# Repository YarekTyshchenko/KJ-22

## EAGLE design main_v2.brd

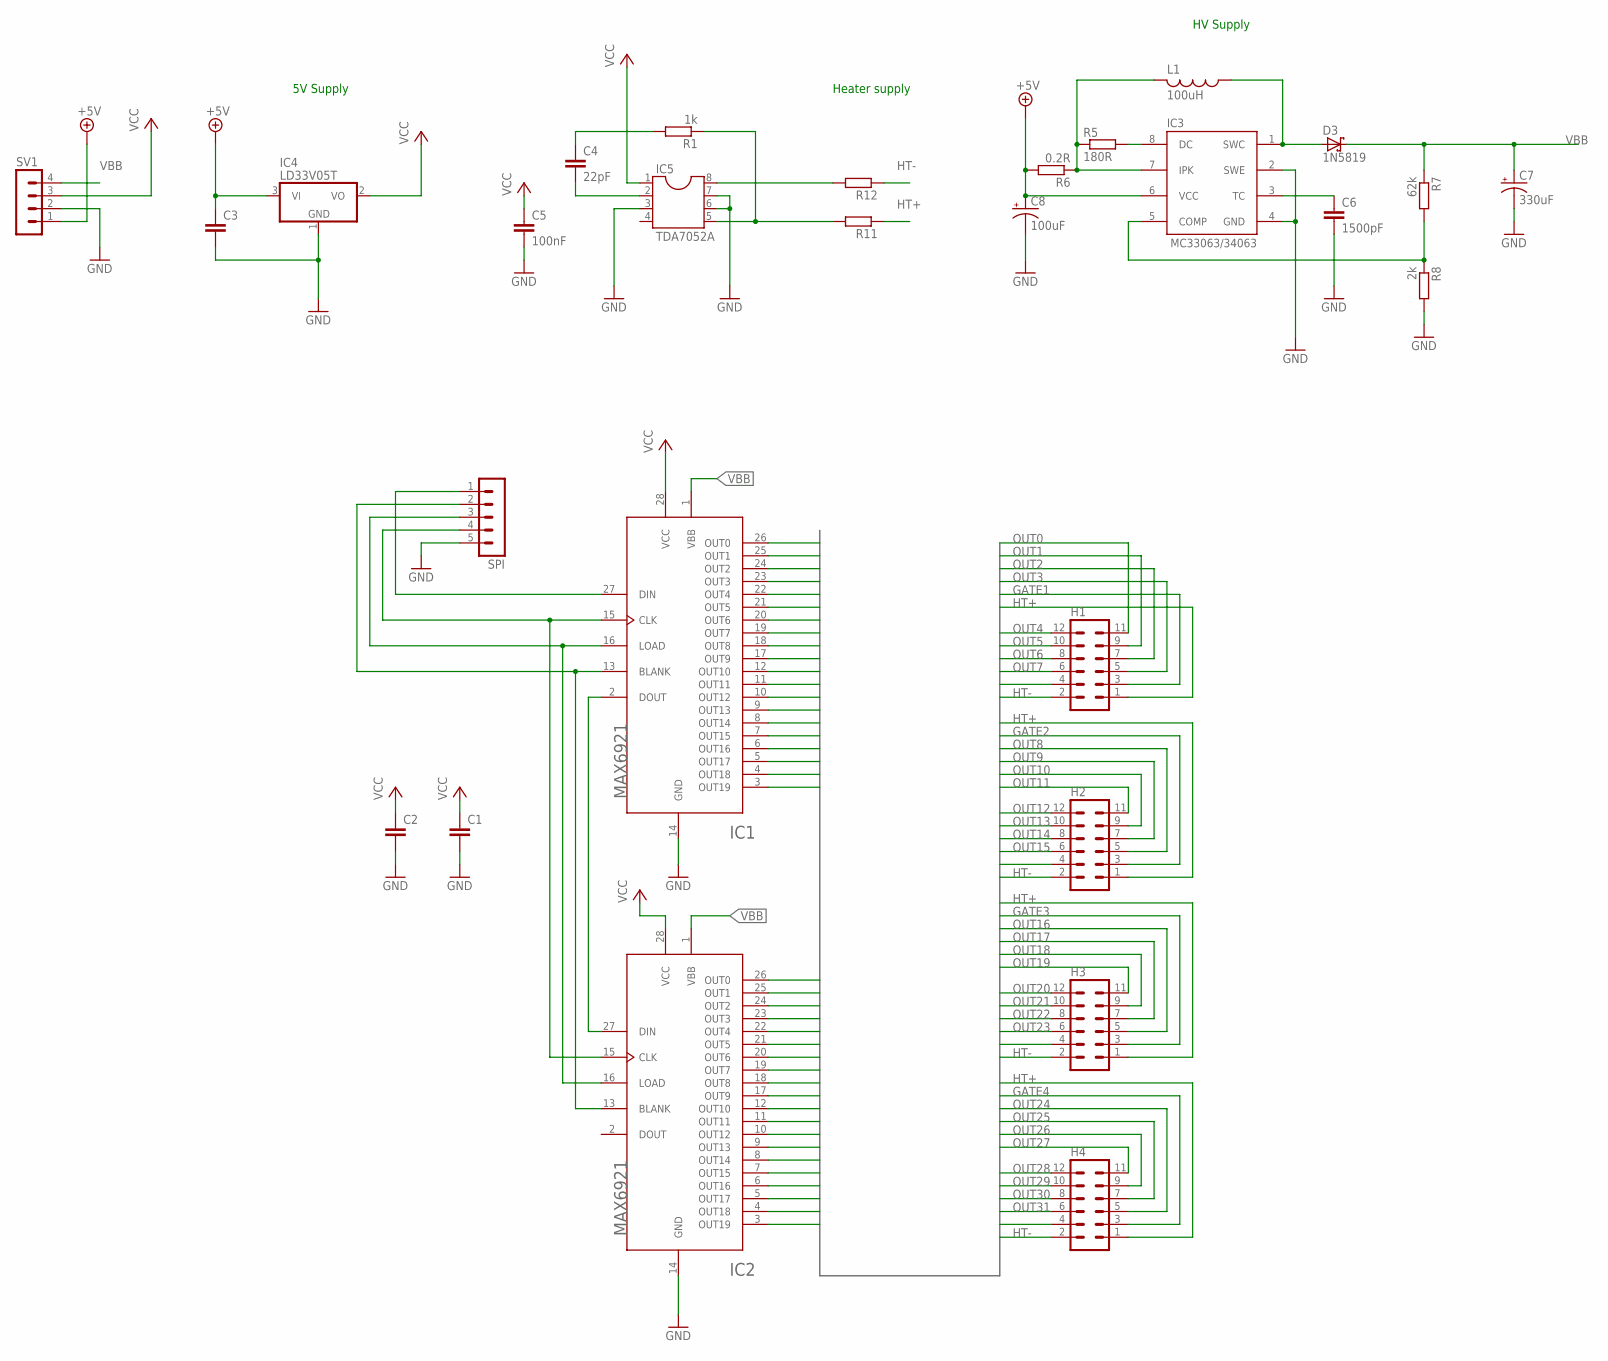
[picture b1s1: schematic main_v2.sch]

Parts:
C1, C2, C3: C-EU025-025X050; C025-025X050
C4: 22pF; C025-025X050
C5: 100nF; C025-025X050
C6: 1500pF; C025-025X050
C7: 330uF; E3,5-8
C8: 100uF; E2,5-5
D3: 1N5819; DO35-7
H1, H2, H3, H4: MA06-2
IC1, IC2: MAX6921; PLCC-S28
IC3: MC33063; DIL08
IC4: LD33V05T; TO220H
IC5: TDA7052A; DIL08
L1: 100uH; 6000-XXXX-RC
R1: 1k; 0204/7
R5: 180R; 0204/7
R6: 0.2R; 0207/10
R7: 62k; 0204/7
R8: 2k; 0204/7
R11, R12: R-EU_0204/7; 0204/7
SPI: MA05-1
SV1: MA04-1

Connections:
+5V: C3.1, C8.+, IC3.6 (VCC), IC4.3 (VI), R6.2, SV1.1
GATE1: H1.3, IC2.12 (OUT10)
GATE2: H2.3, IC2.18 (OUT8)
GATE3: H3.3, IC1.12 (OUT10)
GATE4: H4.3, IC1.25 (OUT1)
GND: C1.2, C2.2, C3.2, C5.2, C6.2, C7.-, C8.-, IC1.14 (GND), IC2.14 (GND), IC3.2 (SWE), IC3.4 (GND), IC4.1 (GND), IC5.3, IC5.6, IC5.7, R8.2, SPI.5, SV1.2
HT+: H1.1, H2.1, H3.1, H4.1, R11.1
HT-: H1.2, H2.2, H3.2, H4.2, R12.1
MOSI: IC1.27 (DIN), SPI.1
unnamed: IC1.2 (DOUT), IC2.27 (DIN)
unnamed: IC5.8, R12.2
unnamed: IC1.13 (BLANK), IC2.13 (BLANK), SPI.2
unnamed: IC1.16 (LOAD), IC2.16 (LOAD), SPI.3
unnamed: C6.1, IC3.3 (TC)
unnamed: IC5.5, R1.1, R11.2
unnamed: D3.A, IC3.1 (SWC), L1.1
unnamed: IC3.7 (IPK), L1.2, R5.1, R6.1
unnamed: IC3.8 (DC), R5.2
unnamed: C4.2, IC5.2
unnamed: IC3.5 (COMP), R7.2, R8.1
unnamed: C4.1, R1.2
OUT0: H1.11, IC2.10 (OUT12)
OUT1: H1.9, IC2.7 (OUT15)
OUT2: H1.7, IC2.5 (OUT17)
OUT3: H1.5, IC2.11 (OUT11)
OUT4: H1.12, IC2.9 (OUT13)
OUT5: H1.10, IC2.8 (OUT14)
OUT6: H1.8, IC2.6 (OUT16)
OUT7: H1.6, IC2.3 (OUT19)
OUT8: H2.5, IC2.21 (OUT5)
OUT9: H2.7, IC2.23 (OUT3)
OUT10: H2.9, IC2.25 (OUT1)
OUT11: H2.11, IC2.19 (OUT7)
OUT12: H2.12, IC2.20 (OUT6)
OUT13: H2.10, IC2.26 (OUT0)
OUT14: H2.8, IC2.24 (OUT2)
OUT15: H2.6, IC2.22 (OUT4)
OUT16: H3.5, IC1.11 (OUT11)
OUT17: H3.7, IC1.8 (OUT14)
OUT18: H3.9, IC1.9 (OUT13)
OUT19: H3.11, IC1.10 (OUT12)
OUT20: H3.12, IC1.7 (OUT15)
OUT21: H3.10, IC1.6 (OUT16)
OUT22: H3.8, IC1.5 (OUT17)
OUT23: H3.6, IC1.3 (OUT19)
OUT24: H4.5, IC1.23 (OUT3)
OUT25: H4.7, IC1.21 (OUT5)
OUT26: H4.9, IC1.22 (OUT4)
OUT27: H4.11, IC1.19 (OUT7)
OUT28: H4.12, IC1.20 (OUT6)
OUT29: H4.10, IC1.18 (OUT8)
OUT30: H4.8, IC1.17 (OUT9)
OUT31: H4.6, IC1.24 (OUT2)
SCK: IC1.15 (CLK), IC2.15 (CLK), SPI.4
SPARE1: H1.4, IC2.4 (OUT18)
SPARE2: H2.4, IC2.17 (OUT9)
SPARE3: H3.4, IC1.4 (OUT18)
SPARE4: H4.4, IC1.26 (OUT0)
VBB: C7.+, D3.C, IC1.1 (VBB), IC2.1 (VBB), R7.1, SV1.4
VCC: C1.1, C2.1, C5.1, IC1.28 (VCC), IC2.28 (VCC), IC4.2 (VO), IC5.1, SV1.3

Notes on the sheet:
Heater supply
HV Supply
5V Supply

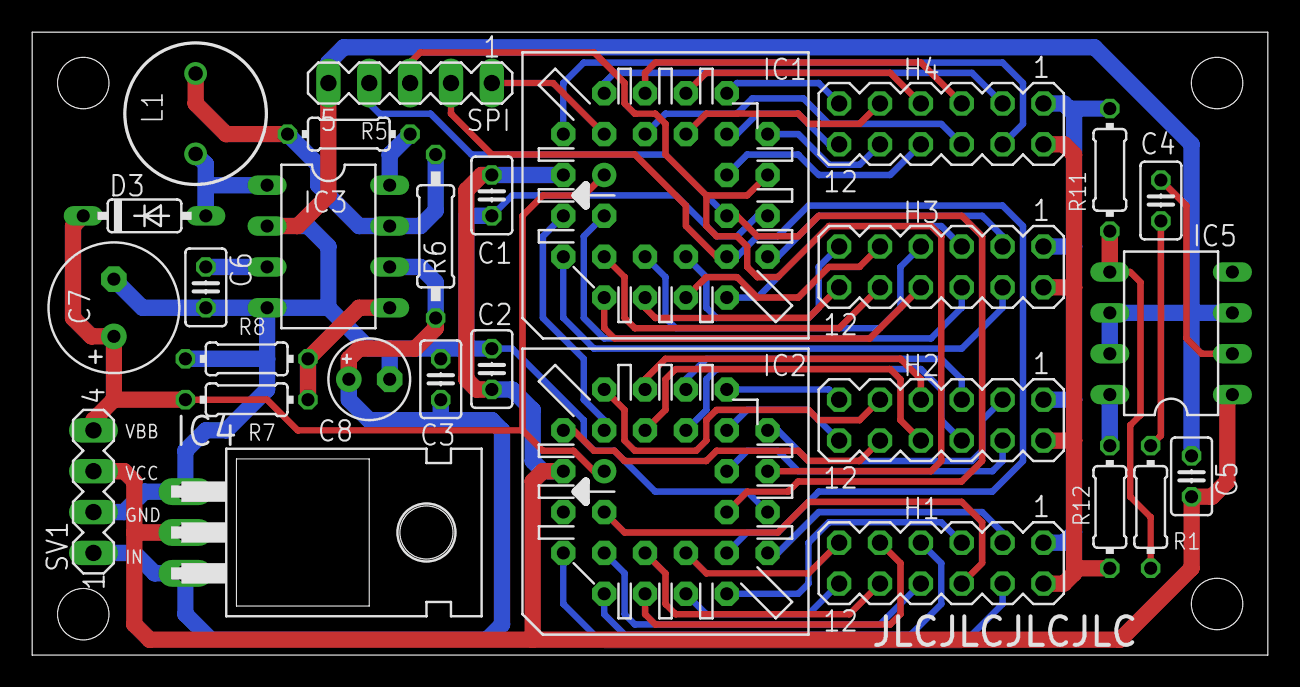
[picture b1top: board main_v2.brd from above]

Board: 2 copper layers, 76.8 x 38.7 mm, 28 parts (0 on the bottom side), 60 nets.

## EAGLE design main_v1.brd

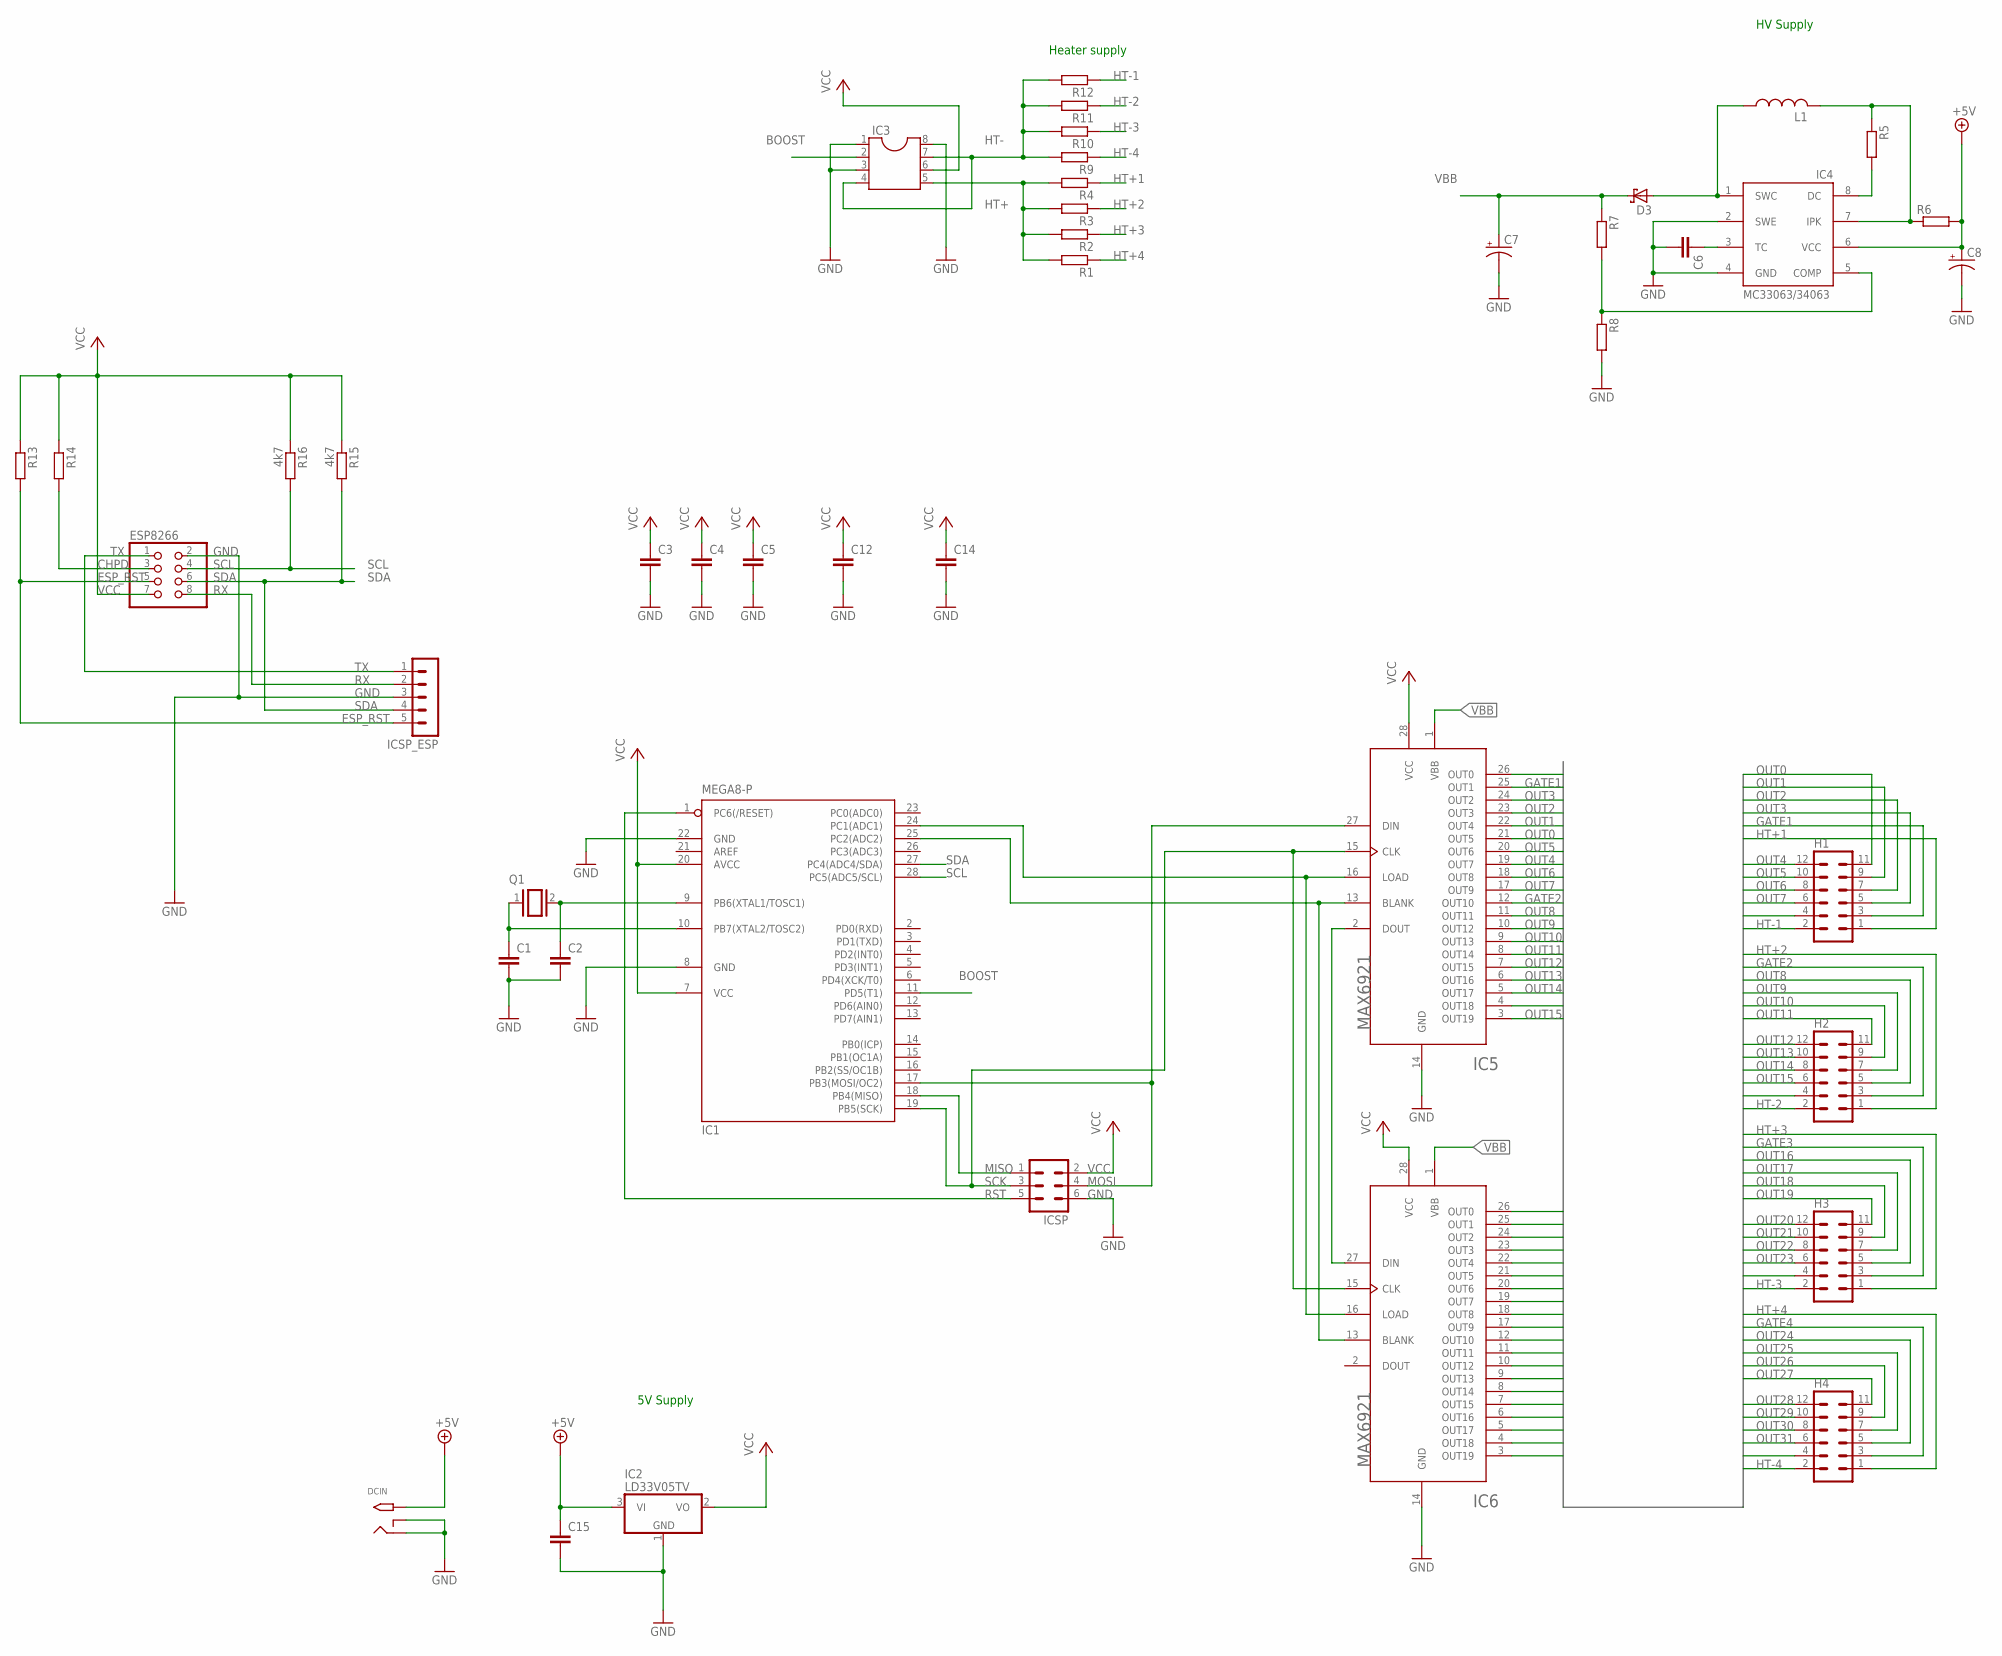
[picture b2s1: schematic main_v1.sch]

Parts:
C1, C2: C2.5/2; C2.5-2
C3, C4, C5, C6, C12, C14, C15: C-EU025-025X050; C025-025X050
C7: CPOL-USE3.5-8; E3,5-8
C8: CPOL-USE2.5-5; E2,5-5
D3: SCHOTTKY-DIODEDO35-7; DO35-7
DCIN: 2.1MMJACKTHM; PJ-102A
ESP8266: PINHD-2X4; 2X04
H1, H2, H3, H4: MA06-2
IC1: MEGA8-P; DIL28-3
IC2: LD33V05TV; TO220V
IC3: DIL8; DIL08
IC4: MC33063/MC34063P; DIL08
IC5, IC6: MAX6921; PLCC-S28
ICSP: MA03-2
ICSP_ESP: MA05-1
L1: L-US6000-XXX-RC; 6000-XXXX-RC
Q1: XTAL/S; QS
R1, R2, R3, R4, R5, R6, R7, R8, R9, R10, R11, R12, R14: R-EU_0204/7; 0204/7
R13: R-EU_0207/10; 0207/10
R15, R16: 4k7; 0204/7

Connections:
+5V: C8.+, C15.1, DCIN.TIP, IC2.3 (VI), IC4.6 (VCC), R6.2
BOOST: IC1.11 (PD5(T1)), IC3.2
CHPD: ESP8266.3, R14.2
ESP_RST: ESP8266.5, ICSP_ESP.5, R13.2
GATE1: H1.3, IC5.25 (OUT1)
GATE2: H2.3, IC5.12 (OUT10)
GATE3: H3.3, IC6.25 (OUT1)
GATE4: H4.3, IC6.12 (OUT10)
GND: C1.2, C2.2, C3.2, C4.2, C5.2, C6.2, C7.-, C8.-, C12.2, C14.2, C15.2, DCIN.RING, DCIN.RING_SW, ESP8266.2, IC1.8 (GND), IC1.22 (GND), IC2.1 (GND), IC3.1, IC3.3, IC3.8, IC4.2 (SWE), IC4.4 (GND), IC5.14 (GND), IC6.14 (GND), ICSP.6, ICSP_ESP.3, R8.2
HT+: IC3.5, R1.2, R2.2, R3.2, R4.2
HT+1: H1.1, R4.1
HT+2: H2.1, R3.1
HT+3: H3.1, R2.1
HT+4: H4.1, R1.1
HT-: IC3.4, IC3.7, R9.2, R10.2, R11.2, R12.2
HT-1: H1.2, R12.1
HT-2: H2.2, R11.1
HT-3: H3.2, R10.1
HT-4: H4.2, R9.1
MISO: IC1.18 (PB4(MISO)), ICSP.1
MOSI: IC1.17 (PB3(MOSI/OC2)), IC5.27 (DIN), ICSP.4
unnamed: IC5.2 (DOUT), IC6.27 (DIN)
unnamed: C1.1, IC1.10 (PB7(XTAL2/TOSC2)), Q1.1
unnamed: IC1.25 (PC2(ADC2)), IC5.13 (BLANK), IC6.13 (BLANK)
unnamed: IC1.24 (PC1(ADC1)), IC5.16 (LOAD), IC6.16 (LOAD)
unnamed: C6.1, IC4.3 (TC)
unnamed: C2.1, IC1.9 (PB6(XTAL1/TOSC1)), Q1.2
unnamed: D3.A, IC4.1 (SWC), L1.1
unnamed: IC4.7 (IPK), L1.2, R5.1, R6.1
unnamed: IC4.8 (DC), R5.2
unnamed: IC4.5 (COMP), R7.2, R8.1
OUT0: H1.11, IC5.21 (OUT5)
OUT1: H1.9, IC5.22 (OUT4)
OUT2: H1.7, IC5.23 (OUT3)
OUT3: H1.5, IC5.24 (OUT2)
OUT4: H1.12, IC5.19 (OUT7)
OUT5: H1.10, IC5.20 (OUT6)
OUT6: H1.8, IC5.18 (OUT8)
OUT7: H1.6, IC5.17 (OUT9)
OUT8: H2.5, IC5.11 (OUT11)
OUT9: H2.7, IC5.10 (OUT12)
OUT10: H2.9, IC5.9 (OUT13)
OUT11: H2.11, IC5.8 (OUT14)
OUT12: H2.12, IC5.7 (OUT15)
OUT13: H2.10, IC5.6 (OUT16)
OUT14: H2.8, IC5.5 (OUT17)
OUT15: H2.6, IC5.3 (OUT19)
OUT16: H3.5, IC6.24 (OUT2)
OUT17: H3.7, IC6.23 (OUT3)
OUT18: H3.9, IC6.22 (OUT4)
OUT19: H3.11, IC6.21 (OUT5)
OUT20: H3.12, IC6.19 (OUT7)
OUT21: H3.10, IC6.20 (OUT6)
OUT22: H3.8, IC6.18 (OUT8)
OUT23: H3.6, IC6.17 (OUT9)
OUT24: H4.5, IC6.11 (OUT11)
OUT25: H4.7, IC6.10 (OUT12)
OUT26: H4.9, IC6.9 (OUT13)
OUT27: H4.11, IC6.8 (OUT14)
OUT28: H4.12, IC6.7 (OUT15)
OUT29: H4.10, IC6.6 (OUT16)
OUT30: H4.8, IC6.5 (OUT17)
OUT31: H4.6, IC6.3 (OUT19)
RST: IC1.1 (PC6(/RESET)), ICSP.5
RX: ESP8266.8, ICSP_ESP.2
SCK: IC1.19 (PB5(SCK)), IC5.15 (CLK), IC6.15 (CLK), ICSP.3
SCL: ESP8266.4, IC1.28 (PC5(ADC5/SCL)), R16.2
SDA: ESP8266.6, IC1.27 (PC4(ADC4/SDA)), ICSP_ESP.4, R15.2
SPARE1: H1.4, IC5.26 (OUT0)
SPARE2: H2.4, IC5.4 (OUT18)
SPARE3: H3.4, IC6.26 (OUT0)
SPARE4: H4.4, IC6.4 (OUT18)
TX: ESP8266.1, ICSP_ESP.1
VBB: C7.+, D3.C, IC5.1 (VBB), IC6.1 (VBB), R7.1
VCC: C3.1, C4.1, C5.1, C12.1, C14.1, ESP8266.7, IC1.7 (VCC), IC1.20 (AVCC), IC2.2 (VO), IC3.6, IC5.28 (VCC), IC6.28 (VCC), ICSP.2, R13.1, R14.1, R15.1, R16.1

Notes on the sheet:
Heater supply
HV Supply
5V Supply

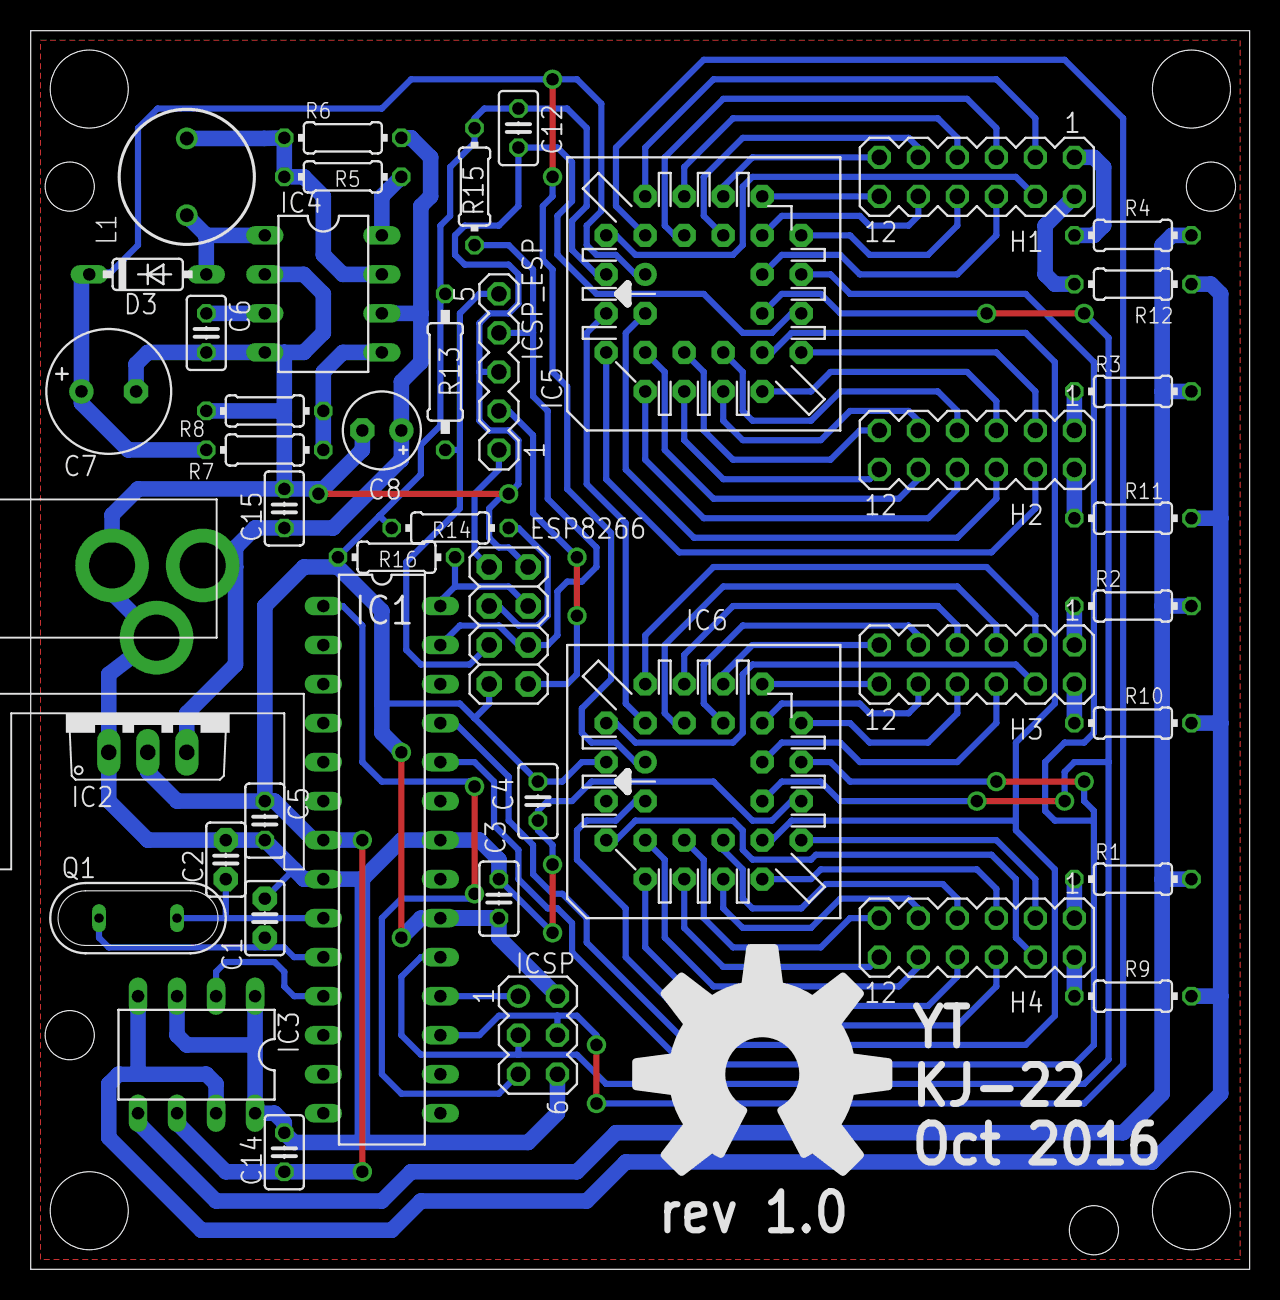
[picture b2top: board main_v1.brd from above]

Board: 2 copper layers, 79.4 x 80.6 mm, 44 parts (0 on the bottom side), 75 nets.

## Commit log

2016-10-17 :confetti_ball: Added .gitattributes & .gitignore files
2016-10-17 Prettify
2016-10-17 Holes and logo fix
2016-10-18 Added better OSHW logo
2016-10-18 Fix OSHPark complaints
2016-10-22 Add software part of the project
2016-10-22 Add creds file
2017-06-12 WIP Add a header for future expansion
    Possible network connectivity, not sure how this is supposed to work
2018-06-10 Prepare to move the atmega
2018-06-10 Move ESP ICSP header, and bits into the board
2018-06-11 Fix ESP socket connections
2018-06-11 Fix some trace widths
2018-06-11 Replace LM7805 with LD33v
2018-06-11 swapped a few ground traces around
2018-06-11 Move the ground pours back
2018-06-11 Align traces
2019-01-28 Add box to repo
2021-04-15 Add a smaller version of the board
2021-04-15 Pracical modifications
2021-04-15 Try wiring a few routes
2021-04-16 Wire most of the board
2021-04-17 More work on the board
2021-04-18 Nearly there
2021-04-18 Try SPI header vertically
2021-04-18 Well, its finished
2021-04-18 Tweaks
2021-04-18 Final Touches
2021-05-15 Add box
2021-05-15 Make box work
2021-05-15 All the holes are there
    Maybe except some mounting pilot holes
2021-05-18 Finished all the holes and measures
2021-05-18 Add 5.7mm and 6mm designs
2021-05-18 Add square mounting brackets, and dxf
2021-05-18 Some sort of changes
2021-05-18 Dont know why this is modified
2021-09-22 Add various laser cut box files
2021-09-22 Add final software
2021-09-22 Add Software
2021-09-27 Implement dimming
2021-09-27 Fix the brightness logic
2021-11-17 Fix Settings overwriting each other
